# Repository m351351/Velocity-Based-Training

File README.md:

# Velocity-Based Training (VBT) - Device

[Suomeksi](README.md) | [In English](README_eng.md)

---

Tämä projekti on osa Oulun ammattikorkeakoulun tieto- ja viestintätekniikan toisen vuoden kevään elektroniikan sovellusprojekti-kurssia (2026). Projektin kesto on 7 viikkoa.

## Sisällysluettelo
* [Yleiskuvaus](#yleiskuvaus)
* [Laitteisto ja komponentit](#laitteisto-ja-komponentit)
* [Ohjelmisto ja teknologiat](#ohjelmisto-ja-teknologiat)
* [Toiminnallisuus](#toiminnallisuus)
* [Projektin hallinta](#projektin-hallinta)
* [Kuvat](#kuvat)

---

## Yleiskuvaus
Projektin tavoitteena on suunnitella ja toteuttaa Velocity-Based Training (VBT) -laite. Laite on tarkoitettu painonnostoon, jossa se mittaa levytangon liikettä ja antaa nostajalle reaaliaikaista palautetta noston nopeudesta ja räjähtävyydestä. 

Laite kiinnitetään tankoon, ja se lähettää kiihtyvyysdataa langattomasti Android-puhelimeen, joka visualisoi tiedon käyttäjälle graafisessa muodossa.

## Posteri
Juliste tarjoaa tiivistetyn yleiskuvan projektin tavoitteista, menetelmistä ja keskeisistä tuloksista.

## Laitteisto ja komponentit
Piirilevy (PCB) on suunniteltu **KiCadilla** noudattaen **Aislerin** suunnittelusääntöjä: [aisler-support](https://github.com/AislerHQ/aisler-support). Laitteen sydämenä toimii ESP32-mikrokontrolleri.

### Komponenttilista:
* **Mikrokontrolleri:** ESP32 C3 Supermini
* **Anturi:** BMI270 (Kiihtyvyysanturi, I2C-väylä)
* **Virranhallinta:** * TP4056 (Latauspiiri)
    * MCP1700 (Regulaattori)

    * Vastukset: R1, R4 (4,7kΩ), R2, R3 (100kΩ), R5 (2,4kΩ), R6, R7 (10kΩ)
    * Kondensaattorit: C1, C2 (1µF), C3, C4 (100nF), C5, C6 (10µF)
* **Akku:** 3,7V litiumpolymeeriakku (Li-Po)
* **Älypuhelin** Huawei Honor View 20 (testikäyttöpuhelin)

## Ohjelmisto ja teknologiat
Projektissa on käytetty nykyaikaisia kehitystyökaluja ja kieliä:

* **Firmware:** ESP32 on ohjelmoitu C++-kielellä käyttäen **VS Codea**.
* **Mobiilisovellus:** Käyttöliittymä on toteutettu **Flutterilla** (Dart).
* **Viestintä:** Laitteen ja puhelimen välinen tiedonsiirto tapahtuu **Bluetooth Low Energy (BLE)** -yhteydellä.
* **Väylät:** ESP32 ja BMI270 kommunikoivat keskenään **I2C**-väylän kautta.

Puhelimeen asennettiin ohjelmisto yhdistämällä puhelin tietokoneeseen USB-kaapelilla ja ajamalla flutterohjelma suoraan puhelimeen. Käyttöjärjestelmän päivitykset ajetaan demovaiheessa suoraan testipuhelimeen.

Laitteen ohjelmistoon on koodattu virrankulutuksen optimointi.

## Toiminnallisuus
1. **Mittaus:** BMI270-anturi lukee tangon kiihtyvyyttä.
2. **Analyysi:** Data lähetetään BLE-yhteyden yli mobiilisovellukseen.
3. **Visualisointi:** Sovellus piirtää kiihtyvyydestä graafia ja laskee noston räjähtävyyden.
4. **Virransäästö:** Akunkestoa optimoidaan ohjelmallisesti asettamalla ESP32 lepotilaan (Deep Sleep), kun laitetta ei käytetä.
5. **Akun seuranta:** Käyttöliittymästä voi seurata reaaliajassa laitteen akun varaustilaa.

## Projektin hallinta
Projekti toteutettiin ketterillä menetelmillä ja se sisälsi seuraavat vaiheet:
* Vaatimusmäärittely ja projektisuunnitelman laatiminen.
* Sulautetun laitteen elektroniikan ja layout-suunnittelun.
* Ohjelmiston toteutuksen (Firmware & Mobile).
* Prototyypin testauksen ja käyttöönoton.

---

## Kuvat

### Piirilevyn valmistus

Kuvassa piirilevy on upotettu pahvimuottiin, jonka päälle stensiili saadaan asetettua tiiviisti piirilevyä vasten pastan levitystä varten.

Komponentit aseteltiin piirilevylle käsin.

BMI270 komponentti on pieni ja sen padit ovat osan pohjassa, joten sen kanssa piti olla erityisen tarkka asetellessa sitä piirilevylle.

Valmis ja uunitettu piirilevy sekä akku.

https://github.com/user-attachments/assets/68aac730-3347-450c-992c-2d826667e670

Video käyttöliittymästä

### Järjestelmäkaavio
**

## Tulevaisuus
Tulevaisuudessa ohjelmistoa on tarkoitus kehittää niin, että eri nostoliikkeistä (takakyykky, maastaveto, penkkipunnerrus, tempaus, rinnalleveto ja rinnalleveto + työntö) on olemassa valmiit datasetit joiden perusteella ohjelma pystyy antamaan selkeän palautteen onko suoritus onnistunut ja mikä on nostajan kehityskaari. Tässä vaiheessa pääpaino on siinä, että laite toimii luotettavasti ja tehokkaasti, pystyy siirtämään ja näyttämään dataa reaaliaikaisesti, sekä seuraamaan akun varausta.

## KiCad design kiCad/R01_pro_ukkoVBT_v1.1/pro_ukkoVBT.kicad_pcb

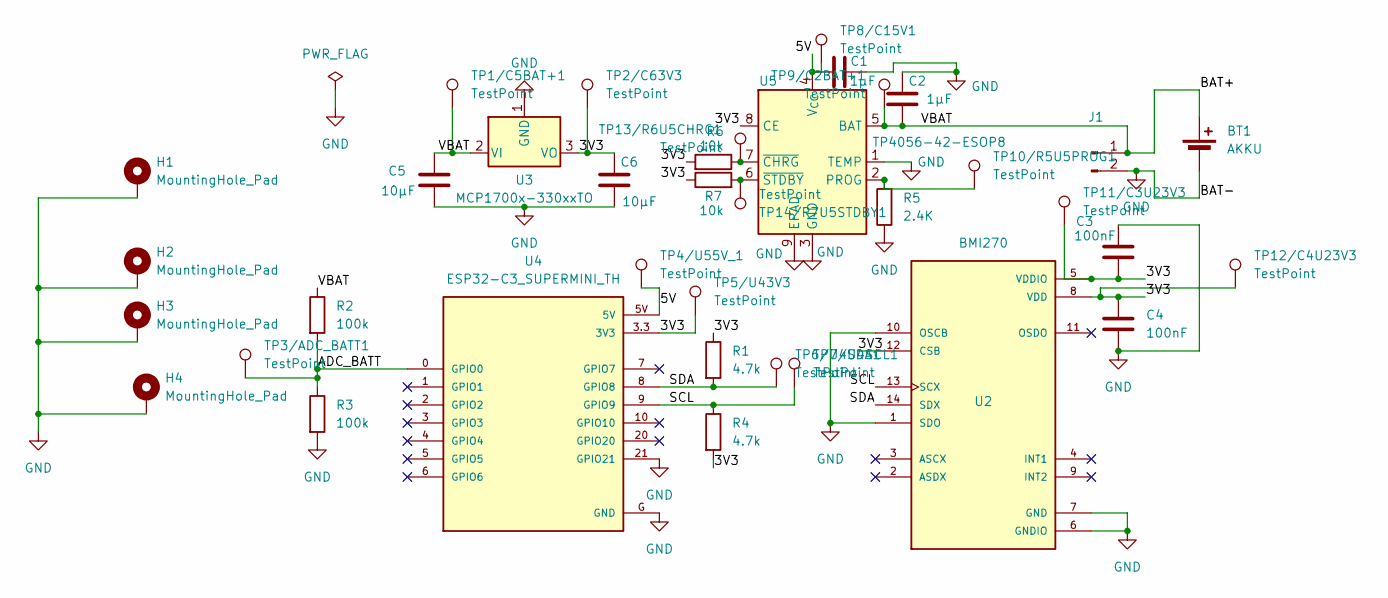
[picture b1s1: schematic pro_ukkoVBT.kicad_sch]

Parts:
BT1: AKKU
C1, C2: 1µF; C_0603_1608Metric
C3, C4: 100nF; C_0603_1608Metric
C5, C6: 10µF; C_0603_1608Metric
H1, H2, H3, H4: MountingHole_Pad; MountingHole_2.2mm_M2_Pad
J1: Conn_01x02_Pin; PinHeader_1x02_P2.54mm_Vertical
R1, R4: 4.7k; R_0603_1608Metric
R2, R3: 100k; R_0603_1608Metric
R5: 2.4K; R_0603_1608Metric
R6, R7: 10k; R_0603_1608Metric
TP1/C5BAT+1, TP2/C63V3, TP3/ADC_BATT1, TP4/U55V_1, TP5/U43V3, TP6/U4SDA1, TP7/U4SCL1, TP8/C15V1, TP9/C2BAT+1, TP10/R5U5PROG1, TP11/C3U23V3, TP12/C4U23V3, TP13/R6U5CHRG1, TP14/R7U5STDBY1: TestPoint; TestPoint_Pad_1.5x1.5mm
U2: BMI270; XDCR_BMI270
U3: MCP1700x-330xxTO; TO-92_Inline
U4: ESP32-C3_SUPERMINI_TH; MODULE_ESP32-C3_SUPERMINI_TH
U5: TP4056-42-ESOP8; SOIC-8-1EP_3.9x4.9mm_P1.27mm_EP2.41x3.3mm_ThermalVias

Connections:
/3V3: C3.2, C4.1, C6.1, R1.1, R4.2, R6.2, R7.1, TP2/C63V3.1, TP5/U43V3.1, TP11/C3U23V3.1, TP12/C4U23V3.1, U2.5 (VDDIO), U2.8 (VDD), U2.12 (CSB), U3.3 (VO), U4.3.3 (3V3), U5.8 (CE)
/5V: C1.1, TP4/U55V_1.1, TP8/C15V1.1, U4.5V, U5.4 (V_{CC})
/ADC_BATT: R2.2, R3.1, TP3/ADC_BATT1.1, U4.0 (GPIO0)
/BAT+: BT1.1 (+), C2.1, C5.1, J1.1, R2.1, TP1/C5BAT+1.1, TP9/C2BAT+1.1, U3.2 (VI), U5.5 (BAT)
/SCL: R4.1, TP7/U4SCL1.1, U2.13 (SCX), U4.9 (GPIO9)
/SDA: R1.2, TP6/U4SDA1.1, U2.14 (SDX), U4.8 (GPIO8)
GND: BT1.2 (-), C1.2, C2.2, C3.1, C4.2, C5.2, C6.2, H1.1, H2.1, H3.1, H4.1, J1.2, R3.2, R5.1, U2.1 (SDO), U2.6 (GNDIO), U2.7 (GND), U2.10 (OSCB), U3.1 (GND), U4.21 (GPIO21), U4.G (GND), U5.1 (TEMP), U5.3 (GND), U5.9 (EPAD)
unnamed: R5.2, TP10/R5U5PROG1.1, U5.2 (PROG)
unnamed: R6.1, TP13/R6U5CHRG1.1, U5.7 (~CHRG)
unnamed: R7.2, TP14/R7U5STDBY1.1, U5.6 (~STDBY)

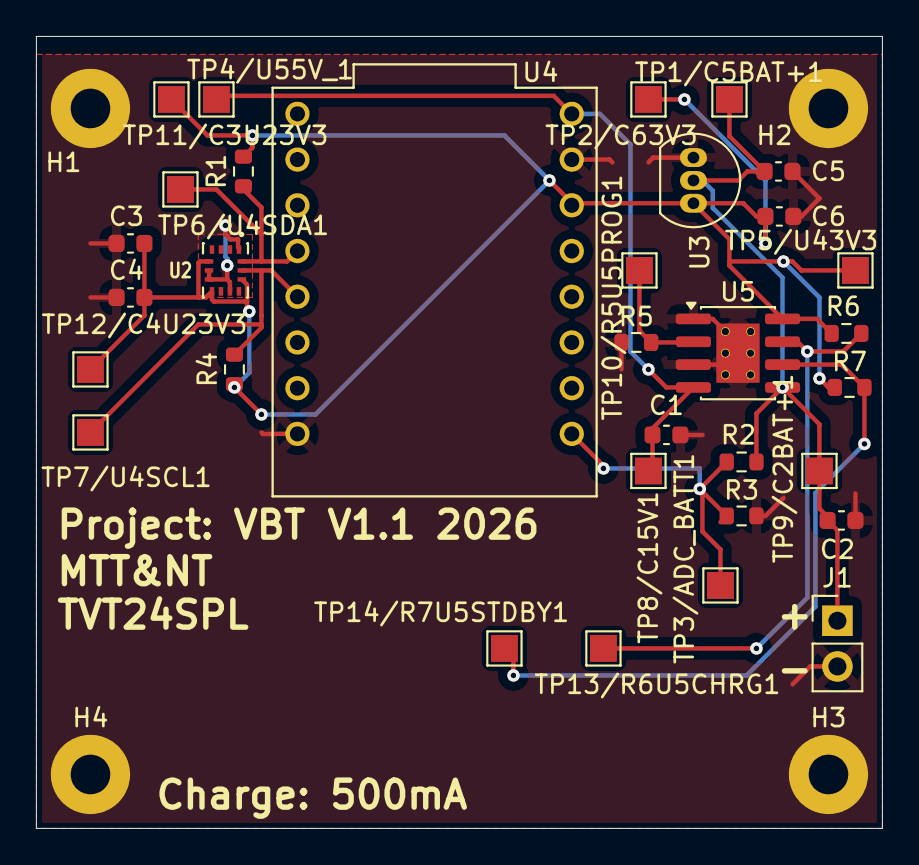
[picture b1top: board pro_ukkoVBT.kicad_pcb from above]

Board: 2 copper layers, 47.0 x 44.0 mm, 36 parts (0 on the bottom side), 10 nets.

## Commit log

2026-03-09 Initial project setup and documentation
    Added gitignore
    Added project plan and work hours template
    Added meeting agenda template
2026-03-19 updated project plan, version 0.01
2026-03-19 docs: add implementation block diagram and component datasheets
2026-03-19 pic added to README
2026-03-19 Added flutter folder containing the UI skeleton
2026-03-19 Fix .gitignore to correctly exclude flutter build and tool folders
2026-03-19 Cleanup: permanently remove build and tool folders from GitHub
2026-03-19 RESTORED: Missing lib folder, pubspec.yaml, and tests
2026-03-20 Lisätty kytkentäkaaviohakemisto ja dokumentaatiota
2026-03-20 added README and gitignore back to main
2026-03-24 saved data before merge
    backend and database created
2026-03-24 flutter: add mock live velocity chart
2026-03-24 feat: added start/stop/reset with mean and peak values
2026-03-24 feat: add analysis for different zones
2026-03-24 added a mock/BLE data source toggle + rearranged code
2026-03-24 added basic BLE connectivity and update the UI with connect/disconnect controls
2026-03-24 Added scanning method for BLE, changes in UI buttons
2026-03-24 tested and working database - UI connection
2026-03-25 feat: lisätty eri kategorioihin painonnosto/voimanostoliikkeet ja päivitetty käyttöliittymää paremmaksi
2026-03-26 UI: Karsittu turhuuksia ja tehty yksinkertaisemmaksi
2026-03-27 UI: muutoksia android version yhteensopivuuteen
2026-03-27 docs: poistettu vanhan anturin datasheet, lisätty uusi
2026-03-31 added kicad pcd design and other related files
2026-03-31 Siivottu kansiorakennetta ja poistettu turhat tiedostot
2026-04-15 functionin PCB is being made and sending data succesfully to UI
2026-04-16 deleted unfunctioning flutter code and modified cpp for ESP (battery charge state)
2026-04-16 flutter: changes to UI. Added battery percentage
2026-04-16 Merged changes in Flutter
2026-04-16 ESP main.cpp ready
2026-04-17 Optimization: Fixed rate scheduling, changed battery update interval, reworked acceleration handling
2026-04-17 Optimization for IDLE
2026-04-19 Organized code, added comments + minor changes to code
2026-04-20 ESP code made more modulare and easier to read
2026-04-21 Added new physics engine
2026-04-21 Merge branch with Niko's changes and optimize performance
    - Integrated power consumption optimizations
    - Added support for dynamic exercise selection
    - Improved velocity calculation
2026-04-21 typo deleted from platformio.ini
2026-04-21 clean + jerk and snatch added to exercise selection
2026-04-21 UI updated
    rep counter and sound feedback addad
    there is still some fix needed
    - recognize the rep correctly and ignore noise
    - shut BLE connection automatically when device is not in use
    - needs data for motion recognition
2026-04-22 MOTION: haamutoistojen suodatus, lepotilan tunnistus ja toiston debounce logiikkaa muutettu
2026-04-22 merged merinmodulaarit & nikon vbt sekoilut
2026-04-22 lohkokaavio paivitetty
2026-04-22 minor changes to flutter, tried to optimize back squat, which is now working OK. There might be a need to make personalized values to other motions. Check line 76 and change those values to get bette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
2026-04-22 Tallenna automaattisesti generoidut tiedostot ennen mergeä
2026-04-22 updated main. Merged from merinModulaarit
2026-04-22 main.cpp updated
2026-04-22 updated main.dart
2026-04-22 deleted double main.dart
2026-04-23 minor changes to main branch and README.Pics moved to docs folder and poster added to README
2026-04-23 updated path for pics in README
2026-04-23 README also in english
2026-04-23 link to language versions
2026-04-23 error fix for language link
2026-04-23 error in flutter fixed
2026-04-27 Add: Fully commented ESP32 source codes. Refactor: physics engine, fix integration drift and optimized BLE/battery loop.
2026-04-27 Minor changes to comments
2026-04-27 changes to UI
2026-04-27 audio add-ons to yaml
2026-04-28 video added to readme
2026-04-28 Update README by removing video and adding link
    Removed video element from README and added a link.
2026-04-28 Update README_eng.md by removing video and adding link
    Removed video element from README and added a link.
